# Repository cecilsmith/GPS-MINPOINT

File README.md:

# GPS-MINPOINT

This is the project folder for a Spring 2024 EE2361 Final Project.

## Hardware List

- Air530 GPS Module (connected via UART)
- PIC24 Microcontroller
- LCD for User Interaction
- LEDs for Debugging
- Printed/Milled Circuit Board for Components
- Enclosure for Electronics and Antenna
- Power Supply (3.3V)

## Software Requirements

- GPS driver ([`gps.h`](/2_Code/src/gps.h)/[`gps.c`](/2_Code/src/gps.c)) to interface with GPS module via UART
- UART driver ([`uart.h`](/2_Code/src/uart.h)/[`uart.c`](/2_Code/src/uart.c)) to handle communication with GPS module
- LCD driver ([`lcd.h`](/2_Code/src/lcd.h)/[`lcd.c`](/2_Code/src/lcd.c)) to handle communication with LCD module
- Mathematical Formulae ([`calculations.h`](/2_Code/src/calculations.h)/[`calculations.c`](/2_Code/src/calculations.c)) to find useful information from GPS coordinates
- General Use Functions ([`utils.h`](/2_Code/src/utils.h)/[`utils.c`](/2_Code/src/utils.c)) to contain non-standard, yet generally useful functions
- [`main.c`](/2_Code/src/main.c) to initialize hardware, call GPS driver to get location data, process data to find location

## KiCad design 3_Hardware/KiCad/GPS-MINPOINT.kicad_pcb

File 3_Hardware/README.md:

# Hardware

This folder contains all work and documentation regarding the hardware. 

For this project, a custom PCB was designed using KiCAD. All footprints, schematics, and 3D files can be found under the `/lib/` folder.

### Current Design:

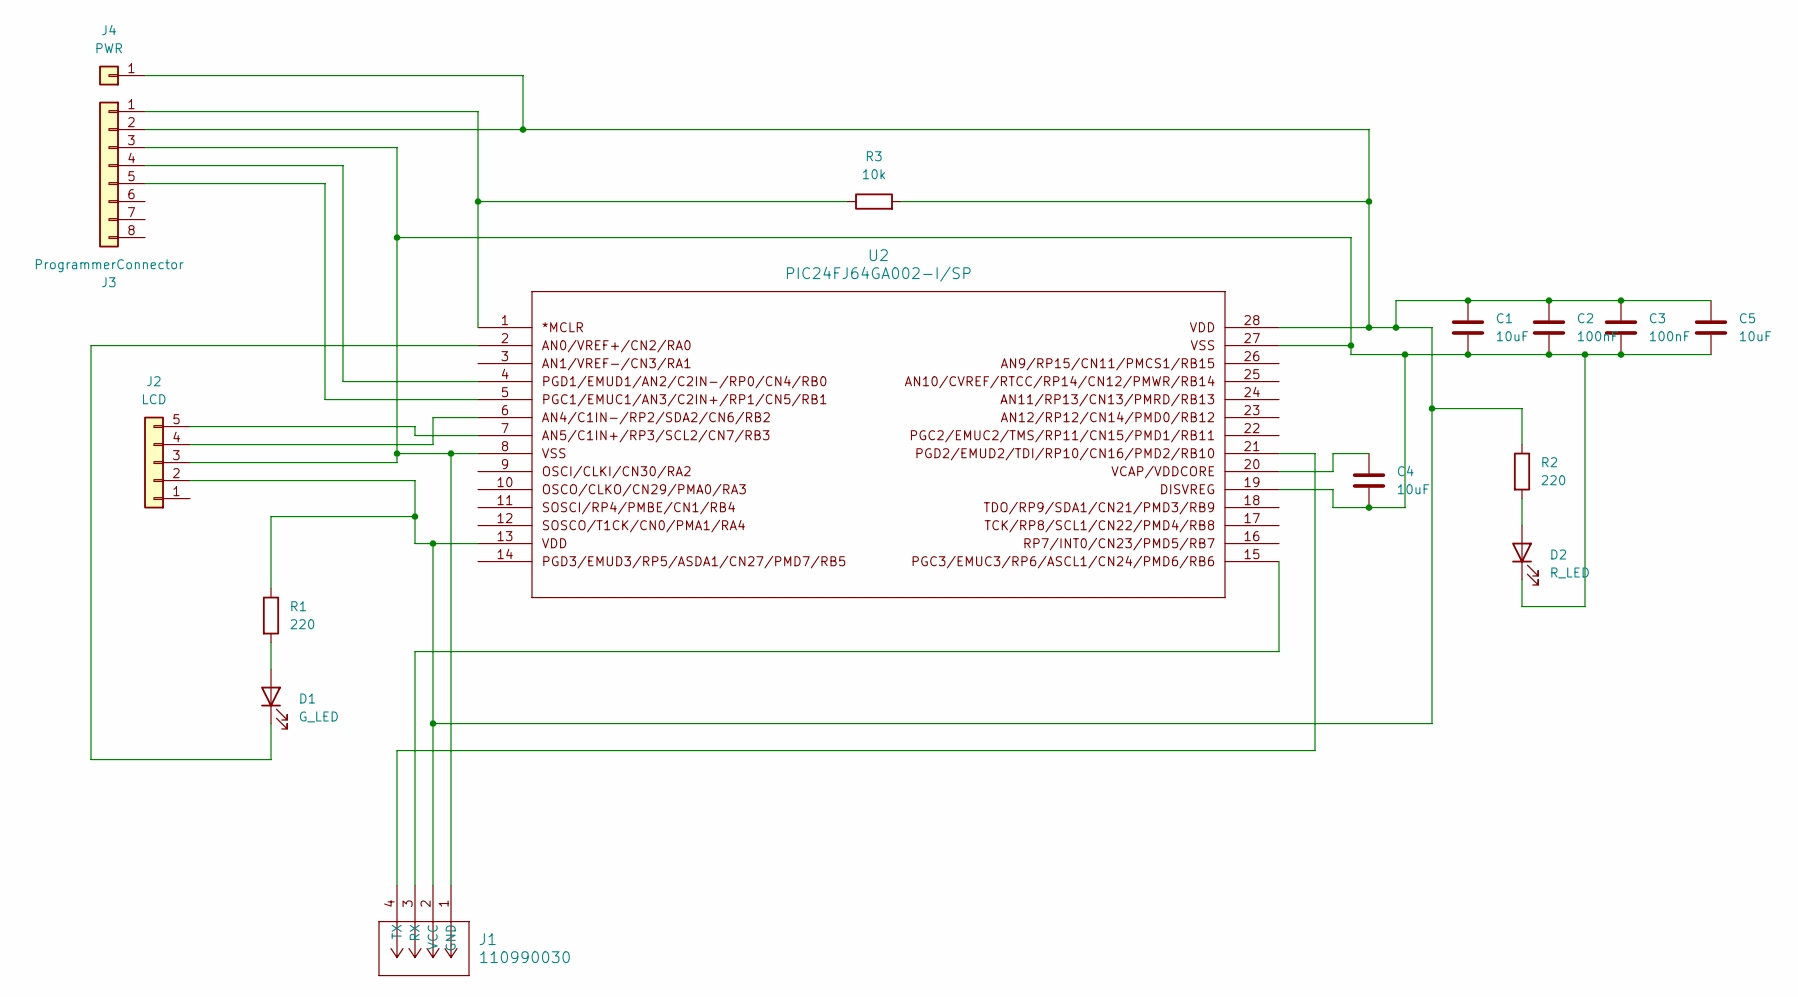
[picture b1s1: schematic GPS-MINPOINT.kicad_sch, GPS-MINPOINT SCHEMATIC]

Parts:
C1, C4, C5: 10uF; C_Disc_D4.7mm_W2.5mm_P5.00mm
C2, C3: 100nF; C_Disc_D4.7mm_W2.5mm_P5.00mm
D1: G_LED; LED_D3.0mm
D2: R_LED; LED_D3.0mm
J1: 110990030; CONN_110990030_SEE
J2: LCD; PinSocket_1x05_P2.54mm_Vertical
J3: ProgrammerConnector; PinHeader_1x08_P2.54mm_Vertical
J4: PWR; PinHeader_1x01_P2.54mm_Vertical
R1, R2: 220; R_Axial_DIN0207_L6.3mm_D2.5mm_P7.62mm_Horizontal
R3: 10k; R_Axial_DIN0207_L6.3mm_D2.5mm_P7.62mm_Horizontal
U2: PIC24FJ64GA002-I/SP; SPDIP28_300MC_MCH

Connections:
unnamed: C4.1, U2.20
unnamed: D1.2 (A), R1.2
unnamed: D1.1 (K), U2.2
unnamed: D2.2 (A), R2.2
unnamed: C1.2, C2.2, C3.2, C4.2, C5.2, D2.1 (K), J1.1 (GND), J2.3 (GND), J3.3, U2.8, U2.19, U2.27
unnamed: J1.3 (RX), U2.15
unnamed: J1.4 (TX), U2.21
unnamed: C1.1, C2.1, C3.1, C5.1, J1.2 (VCC), J2.2 (VDD), J3.2, J4.1, R1.1, R2.1, R3.2, U2.13, U2.28
unnamed: J2.5 (SCL), U2.7
unnamed: J2.4 (SDA), U2.6
unnamed: J3.1, R3.1, U2.1
unnamed: J3.4, U2.4
unnamed: J3.5, U2.5

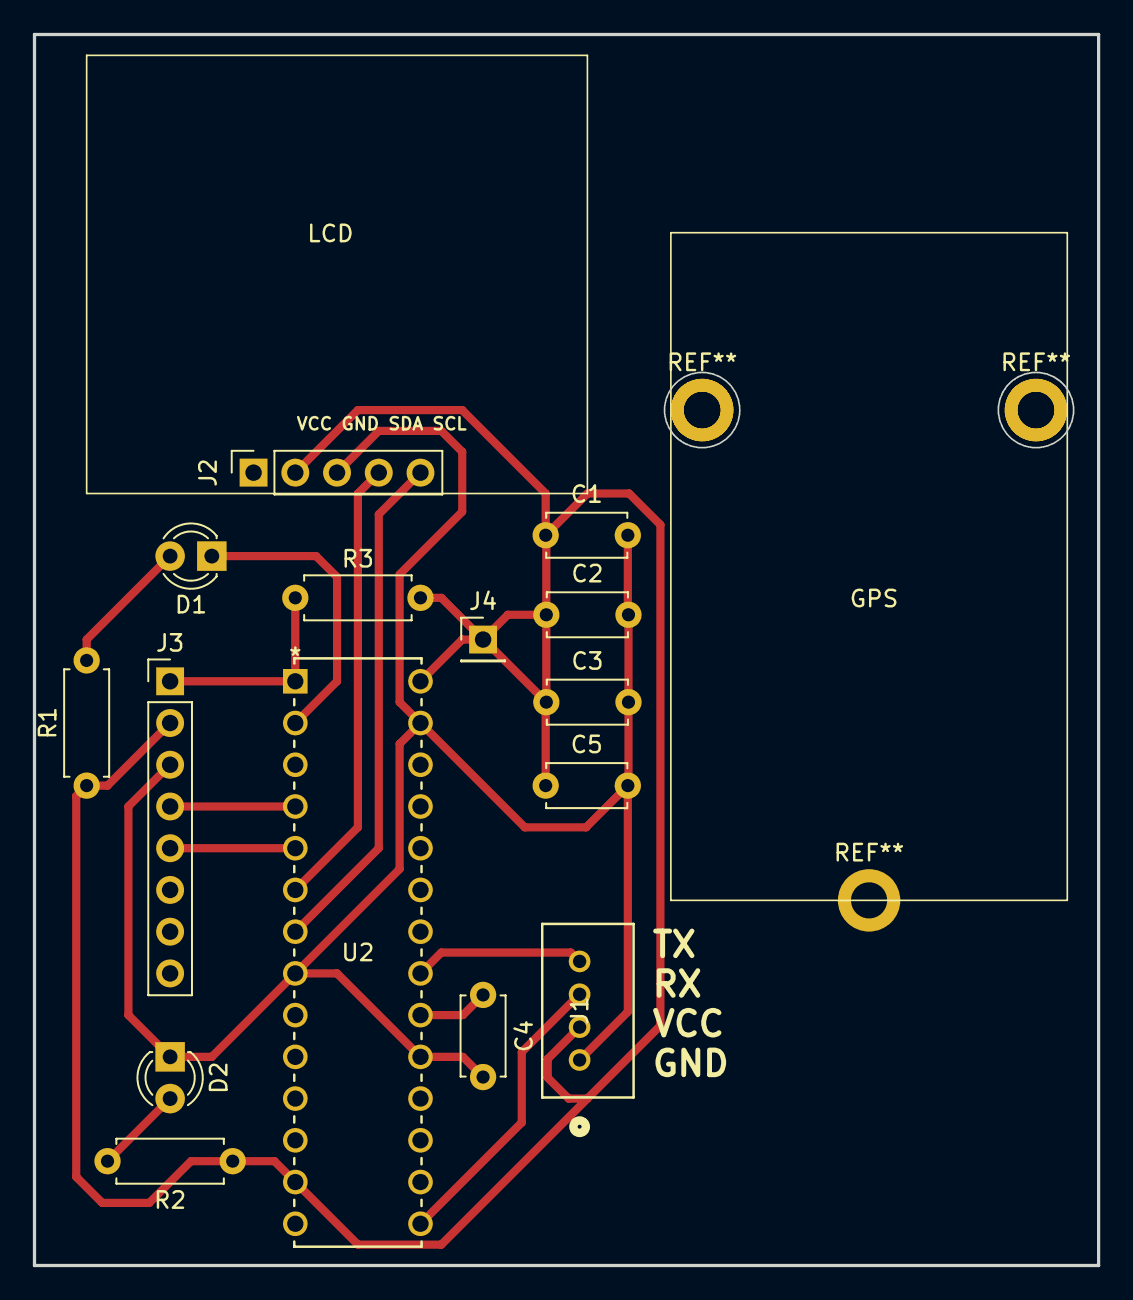
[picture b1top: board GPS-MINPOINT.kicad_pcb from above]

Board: 2 copper layers, 64.8 x 74.9 mm, 15 parts (0 on the bottom side), 13 nets.

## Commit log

2024-03-13 Air530 GPS Module Documentation
2024-03-22 Updates to the repo structure
2024-03-28 Example Push To GitHub
2024-03-29 More documentation/boilerplate code upload
2024-03-29 Further improvements to the initial code
2024-03-29 updates to home README and uart.c
2024-03-29 added GitHub desktop instructions
2024-03-29 restructure for cleanliness
2024-03-31 UART library and header
    basically copy paste disc lol. pls double check maybe????
2024-03-31 Reformatting of the UART code
    My last push wasn't in the same format as the code layout branch so I remade it to match.
2024-04-05 initial schematic push
2024-04-06 Included sending string and also initializing baudrate
    I added a "send string" function and also added baudRate into the initUART.
2024-04-08 Implementations of the suggestions
    I have changed the baudrate calculation so that we can enter 9600 and it automatically calculates it to 103.
    I have also added the unsigned int before baudrate. I was wondering why it was giving an error lol.
    as for the setup/init pin initialization, i removed setting all pins to digital and just kept setting the pins we need (_TRISB6 = 0; _TRISB10 = 1;)
    as for back &= 63, that was originally copied from the discussion to implement a circular buffer. however, it didn't work when i tried implementing it in my lab so i have upddated it to a version tha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
    Finally, I have added a string getter. It requires a pointer string and
2024-04-08 Small fix of the void
    I have changed the unsigned char to void on that one function we looked at together.
2024-04-10 Still a work in progress. I've gotten started on gps initialization. A lot of work remains on setting up the file so that we can do plenty of string manipulation.
2024-04-11 Added additional functions for obtaining longitude and latitude data
2024-04-11 More functions added
2024-04-11 Remade get string function
    remade the get string function so we can always just pull the entire string and you know what the size of the string is too. Also increased the buffer size to 170 so there should be less of a worry t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
2024-04-12 Fixed header file
    My bad oopsies
2024-04-12 Fixed errors caught by MPLABX. Setup a main function for debugging purposes.
2024-04-20 Upload of finished PCB design
2024-04-22 Fully working uart.c and gps.c. Extensively tested and debugged.
    Fully working uart.c and gps.c. Extensively tested and debugged.
2024-04-23 Comments added
    Comments added
2024-04-23 Fixed hardware issues
    Update
2024-04-24 Other files (gps,uart,main)
    Changes to other files to fit the LCD file. Suggested main structure to work, needs some editing to display correctly
2024-04-25 restructure of code for ease of readability
2024-04-25 small update to fix errors
2024-04-25 another oopsie
2024-04-25 added utils.h (delay_ms)
2024-04-25 Fixed calculations to include bearing finder
2024-04-25 Updates and bearing
2024-04-25 updated the header file
2024-04-25 update to main to display coords & distance
2024-04-26 Hardwarre updates
    Yay :) wrkosgn
2024-04-26 low battter
2024-04-26 Updates to typecasting and bool to char for LCD_flag
2024-04-26 Fixed distance calculator
    Accurate to 2 feet now
2024-04-26 documentation overhaul
2024-04-26 change of testbench location
2024-04-26 haverside update
2024-04-26 fixed empty character thing and also dkm
2024-04-26 bearing calculation and 3rd LCD screen.
2024-04-26 fchy
2024-04-29 minor updates to documentation
